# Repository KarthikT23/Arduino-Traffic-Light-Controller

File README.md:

# Arduino-Traffic-Light-Controller
2nd PCB design

# Scmhematic

# PCB 

# 3D View

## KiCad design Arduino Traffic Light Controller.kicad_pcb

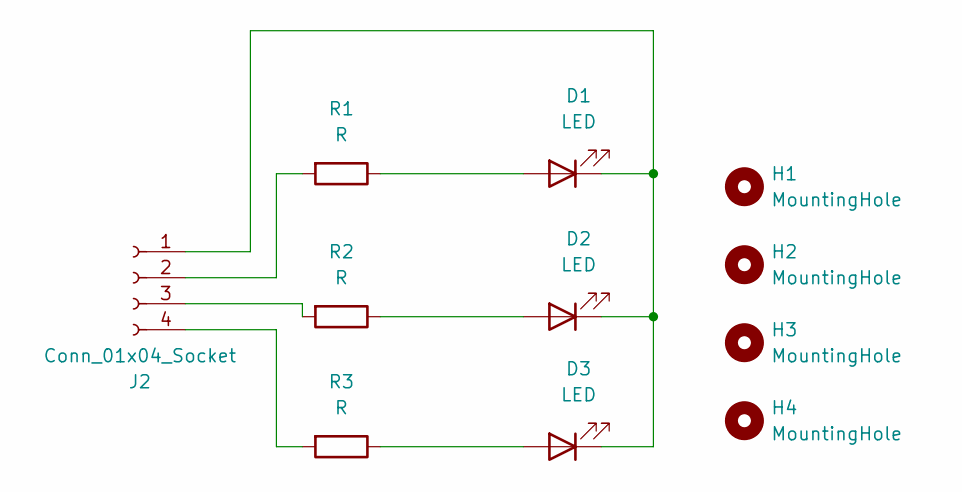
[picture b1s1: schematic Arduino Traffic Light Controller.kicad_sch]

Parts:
D1, D2, D3: LED; LED_D3.0mm
H1, H2, H3, H4: MountingHole; MountingHole_2.5mm
J2: Conn_01x04_Socket; PinHeader_1x04_P2.54mm_Horizontal
R1, R2, R3: R; R_Axial_DIN0204_L3.6mm_D1.6mm_P5.08mm_Horizontal

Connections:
unnamed: D1.2 (A), R1.1
unnamed: D1.1 (K), D2.1 (K), D3.1 (K), J2.1
unnamed: D2.2 (A), R2.1
unnamed: D3.2 (A), R3.1
unnamed: J2.2, R1.2
unnamed: J2.3, R2.2
unnamed: J2.4, R3.2

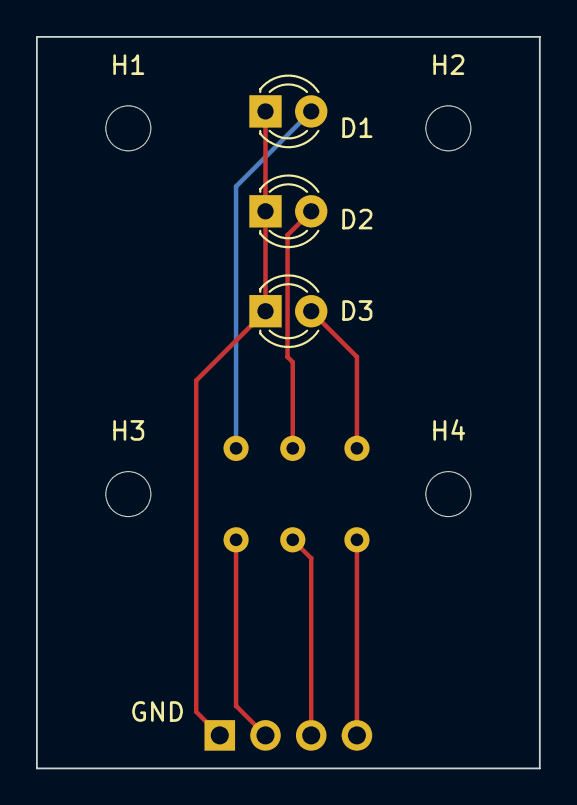
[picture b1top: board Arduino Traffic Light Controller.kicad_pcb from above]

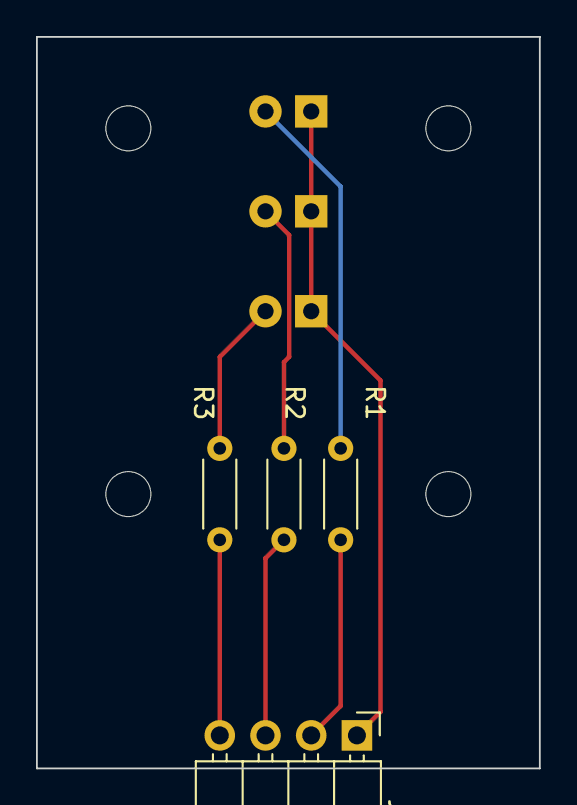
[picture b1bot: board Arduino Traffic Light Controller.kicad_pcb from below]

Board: 2 copper layers, 27.9 x 40.6 mm, 11 parts (4 on the bottom side), 7 nets.
